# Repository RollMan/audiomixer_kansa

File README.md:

## 改善点
- schematic のカップリングコンデンサに極性がなく、PCB のシルクが示すコンデンサのピンアサインが反転している。
- 入出力の 3.5mm フォーンジャックが基板の中程にあるせいで、一部のフォーンジャック、特にハンドル (先端接触部の次にある絶縁体部) が太いジャックが刺さらない。
- 積層セラミックコンデンサのピンピッチ (足幅) が BOM のものと合わない。
- C9, C10 のピンピッチ (足幅) が BOM のものと合わない。

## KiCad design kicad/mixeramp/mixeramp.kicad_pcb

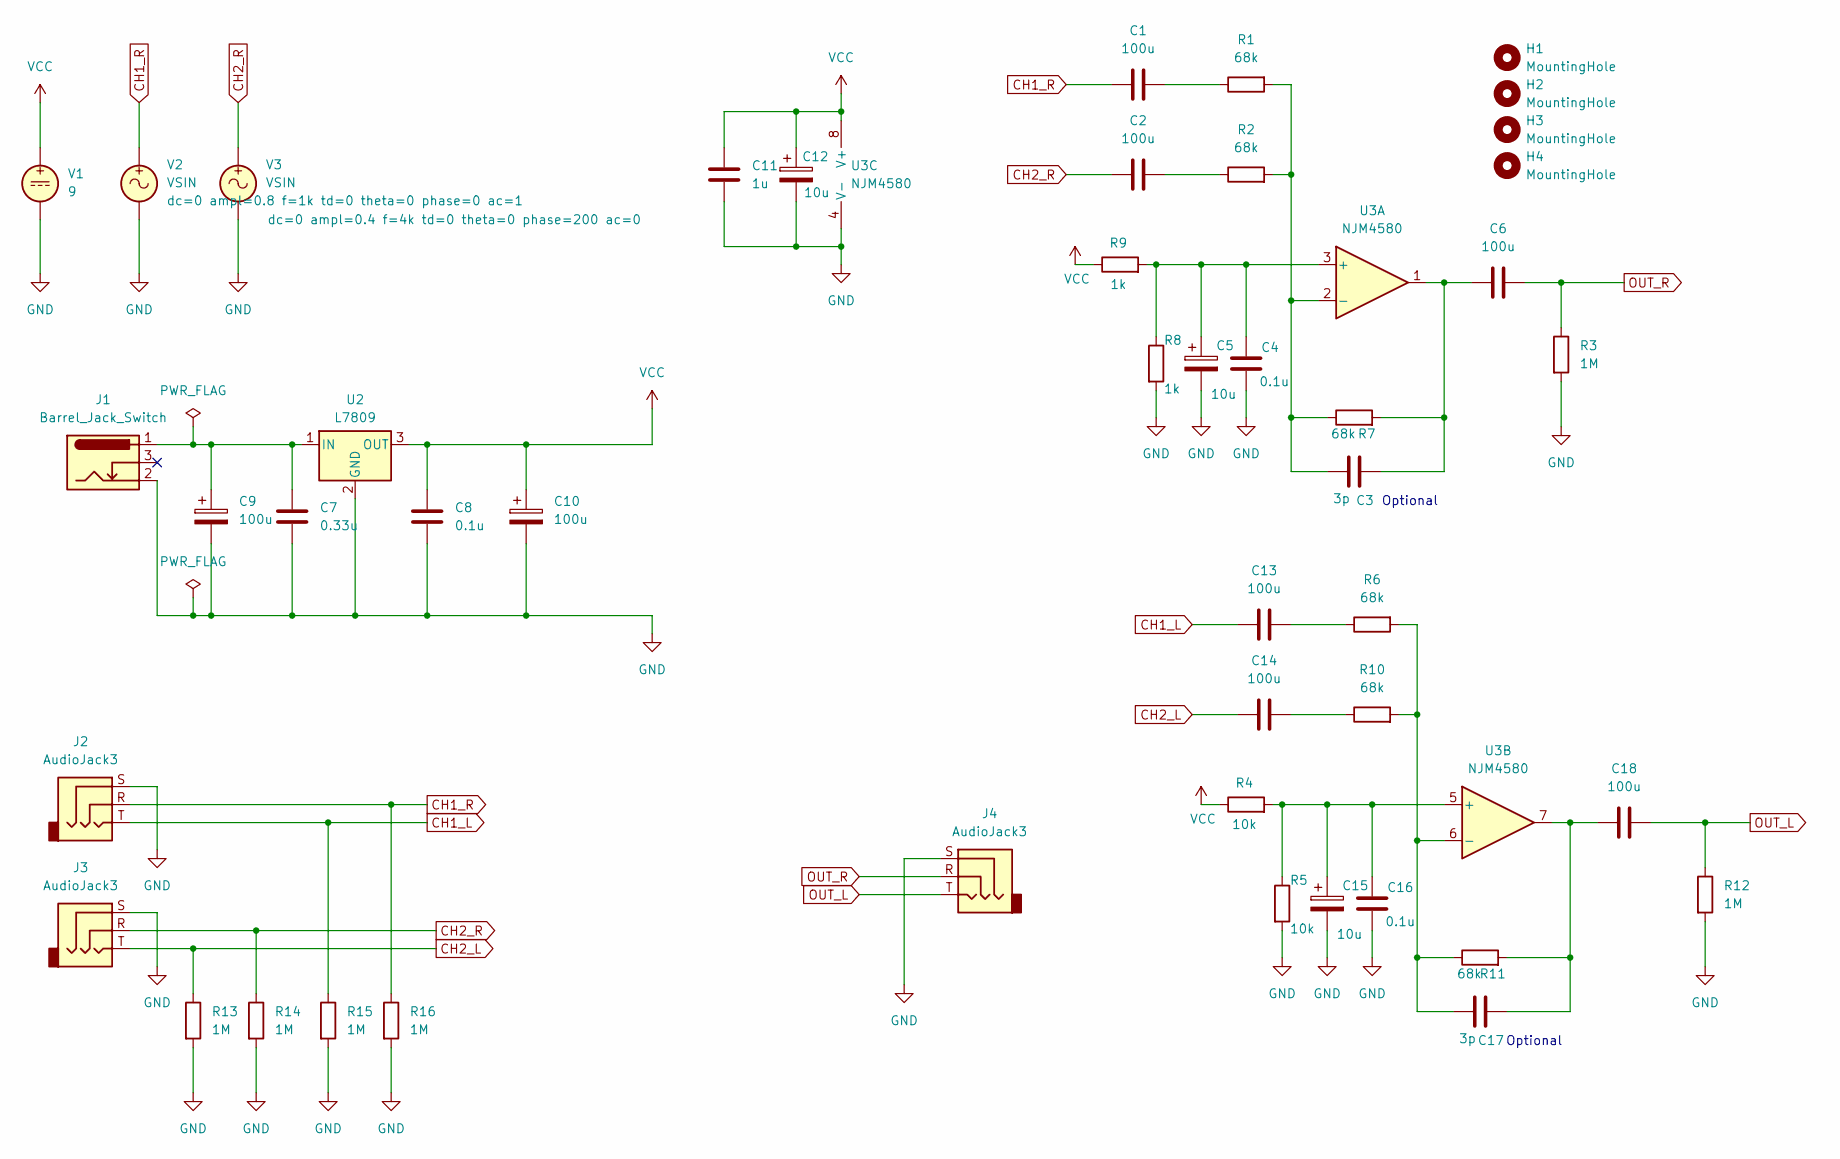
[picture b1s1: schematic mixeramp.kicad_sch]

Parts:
C1, C2, C6, C13, C14, C18: 100u; CP_Radial_D8.0mm_P3.50mm
C3, C17: 3p; C_Disc_D3.8mm_W2.6mm_P2.50mm
C4, C8, C16: 0.1u; C_Disc_D3.8mm_W2.6mm_P2.50mm
C5, C12, C15: 10u; C_Disc_D3.8mm_W2.6mm_P2.50mm; MPN RD20F106Z1EH5L
C7: 0.33u; C_Disc_D3.8mm_W2.6mm_P2.50mm; MPN RD15W334K1HL2L
C9, C10: 100u; CP_Radial_D5.0mm_P2.50mm
C11: 1u; C_Disc_D3.8mm_W2.6mm_P2.50mm
H1, H2, H3, H4: MountingHole; MountingHole_3.2mm_M3
J1: Barrel_Jack_Switch; BarrelJack_Horizontal
J2, J3, J4: AudioJack3; Jack_3.5mm_Switronic_ST-005-G_horizontal; MPN ST-005-G
R1, R2, R6, R10: 68k; R_Axial_DIN0411_L9.9mm_D3.6mm_P15.24mm_Horizontal
R3, R12, R13, R14, R15, R16: 1M; R_Axial_DIN0411_L9.9mm_D3.6mm_P15.24mm_Horizontal
R4, R5: 10k; R_Axial_DIN0411_L9.9mm_D3.6mm_P15.24mm_Horizontal
R7, R11: 68k; R_Axial_DIN0204_L3.6mm_D1.6mm_P2.54mm_Vertical
R8, R9: 1k; R_Axial_DIN0411_L9.9mm_D3.6mm_P15.24mm_Horizontal
U2: L7809; TO-220-3_Vertical; MPN L7809CV
U3: NJM4580; DIP-8_W7.62mm
V1: 9
V2, V3: VSIN

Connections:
CH1_L: C13.1, J2.T, R15.1
CH1_R: C1.1, J2.R, R16.1, V2.1
CH2_L: C14.1, J3.T, R13.1
CH2_R: C2.1, J3.R, R14.1, V3.1
GND: C4.2, C5.2, C7.2, C8.2, C9.2, C10.2, C11.2, C12.2, C15.2, C16.2, J1.2, J2.S, J3.S, J4.S, R3.2, R5.2, R8.2, R12.2, R13.2, R14.2, R15.2, R16.2, U2.2 (GND), U3.4 (V-), V1.2, V2.2, V3.2
unnamed: C1.2, R1.1
unnamed: C2.2, R2.1
unnamed: C3.2, C6.1, R7.2, U3.1
unnamed: C13.2, R6.1
unnamed: C14.2, R10.1
unnamed: C17.2, C18.1, R11.2, U3.7
unnamed: C7.1, C9.1, J1.1, U2.1 (IN)
unnamed: C4.1, C5.1, R8.1, R9.2, U3.3 (+)
unnamed: C3.1, R1.2, R2.2, R7.1, U3.2 (-)
unnamed: C15.1, C16.1, R4.2, R5.1, U3.5 (+)
unnamed: C17.1, R6.2, R10.2, R11.1, U3.6 (-)
OUT_L: C18.2, J4.T, R12.1
OUT_R: C6.2, J4.R, R3.1
VCC: C8.1, C10.1, C11.1, C12.1, R4.1, R9.1, U2.3 (OUT), U3.8 (V+), V1.1

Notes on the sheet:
Optional

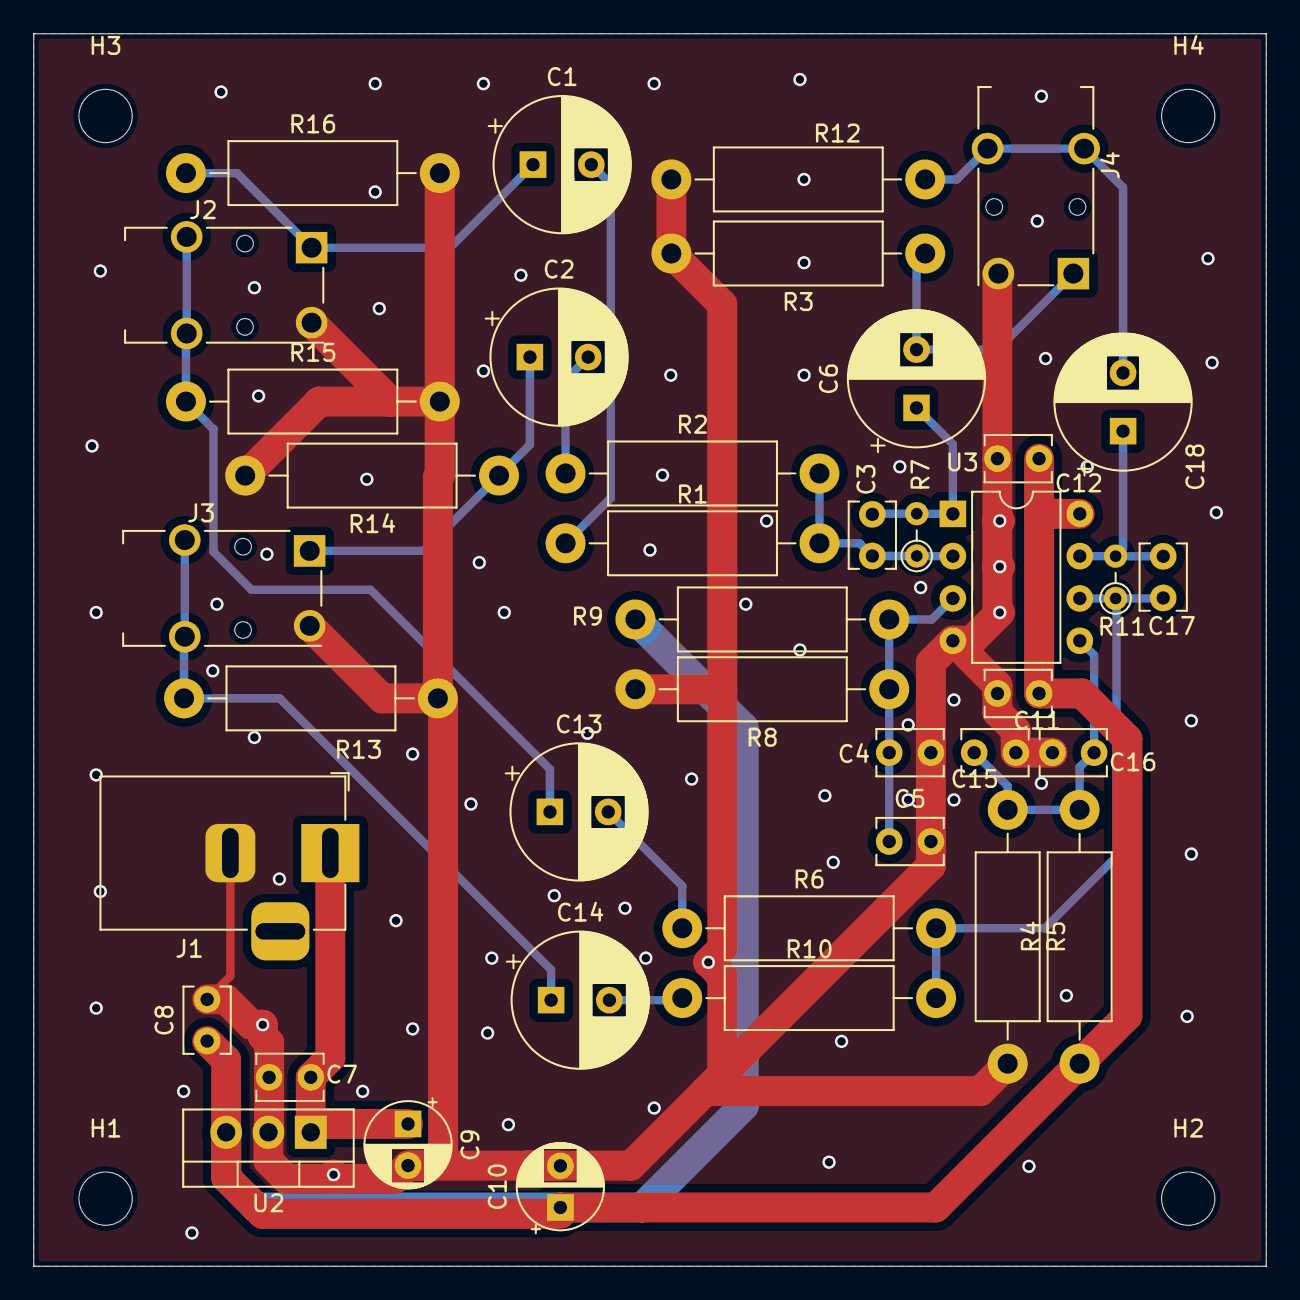
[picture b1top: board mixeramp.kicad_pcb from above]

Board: 2 copper layers, 74.0 x 74.0 mm, 44 parts (0 on the bottom side), 19 nets.

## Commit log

2024-05-26 simulation with buffers at input
2024-05-26 remove buffer
2024-07-29 wip: making BOM and footprint list
2024-07-29 make BOM and footprint list
2024-07-30 place footprints
2024-07-30 add pcb
2024-07-30 change via size constraints
2024-07-31 adjust silkscreen placements
2024-07-31 export gerbers for jlcpcb
2024-07-31 add MPNs for several components
2024-08-17 add improvements
2024-08-17 append improvements
